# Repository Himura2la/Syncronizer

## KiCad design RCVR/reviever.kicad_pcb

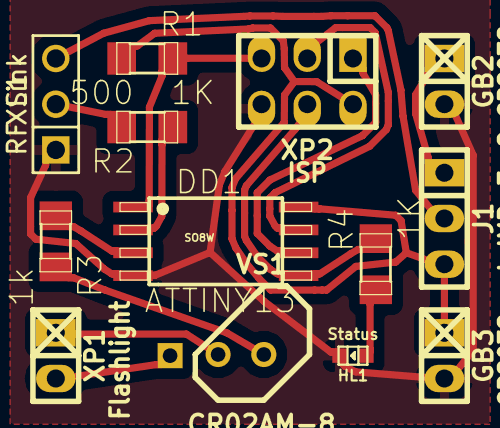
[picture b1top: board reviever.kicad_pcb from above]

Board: 2 copper layers, 13 parts (0 on the bottom side), 15 nets.

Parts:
DD1: ATTINY13; SMD_SO8W_50_300
GB2: 2xCR2032; CONN_PLS-2
GB3: CR2032; CONN_PLS-2
HL1: Status; SMD_Led_0603
J1: J_JMP-3; CONN_PLS-3
R1, R4: 1K; SMD_R_1206
R2: 500; SMD_R_1206
R3: 1k; SMD_R_1206
VS1: CR02AM-8; DISCRET_PACK_TO92-3
XP1: Flashlight; CONN_PLS-2
XP2: ISP; CONN_PLD-6
XS1: RF Link; CONN_PBS-3

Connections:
+3V: DD1.8, GB3.1, J1.3, R1.1, XP2.2
+5V: GB2.1, J1.1
unnamed: DD1.3, R3.1
unnamed: DD1.2, R2.1
unnamed: DD1.1, R1.2, XP2.5
unnamed: J1.2, XS1.3
unnamed: DD1.7, XP2.3
unnamed: DD1.5, R4.2, XP2.4
unnamed: HL1.2, R4.1
unnamed: DD1.6, XP2.1
unnamed: R2.2, XS1.2
unnamed: R3.2, VS1.3
unnamed: VS1.1, XP1.2
unnamed: VS1.2, XP1.1
~: DD1.4, GB2.2, GB3.2, HL1.1, XP2.6, XS1.1

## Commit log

2015-04-05 :space_invader: Added .gitattributes & .gitignore files
2015-04-05 Enter
